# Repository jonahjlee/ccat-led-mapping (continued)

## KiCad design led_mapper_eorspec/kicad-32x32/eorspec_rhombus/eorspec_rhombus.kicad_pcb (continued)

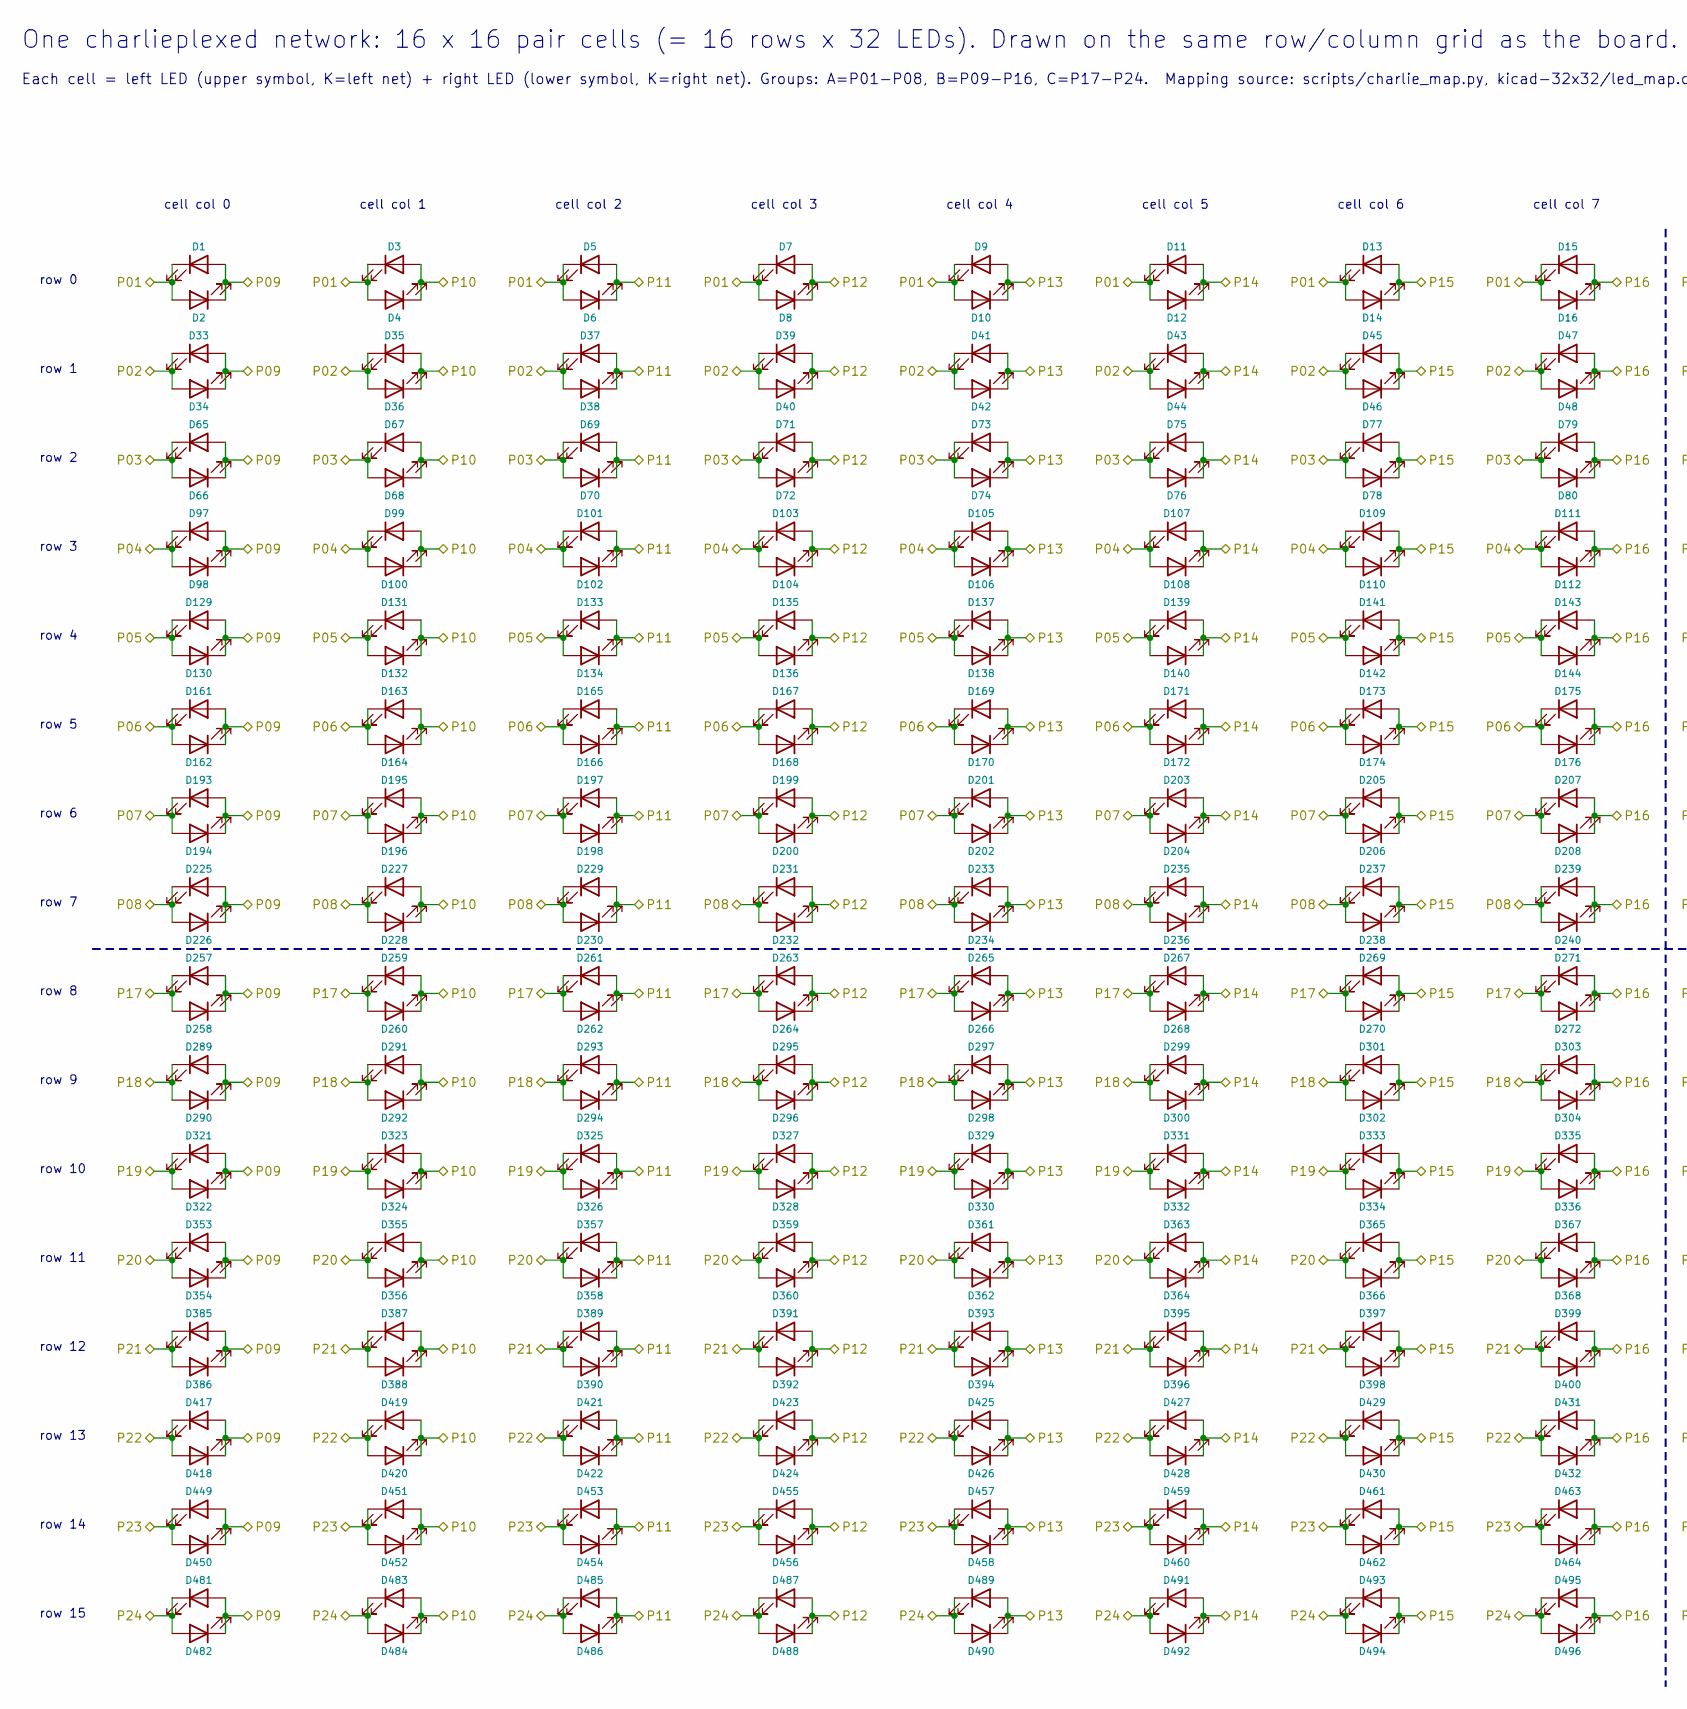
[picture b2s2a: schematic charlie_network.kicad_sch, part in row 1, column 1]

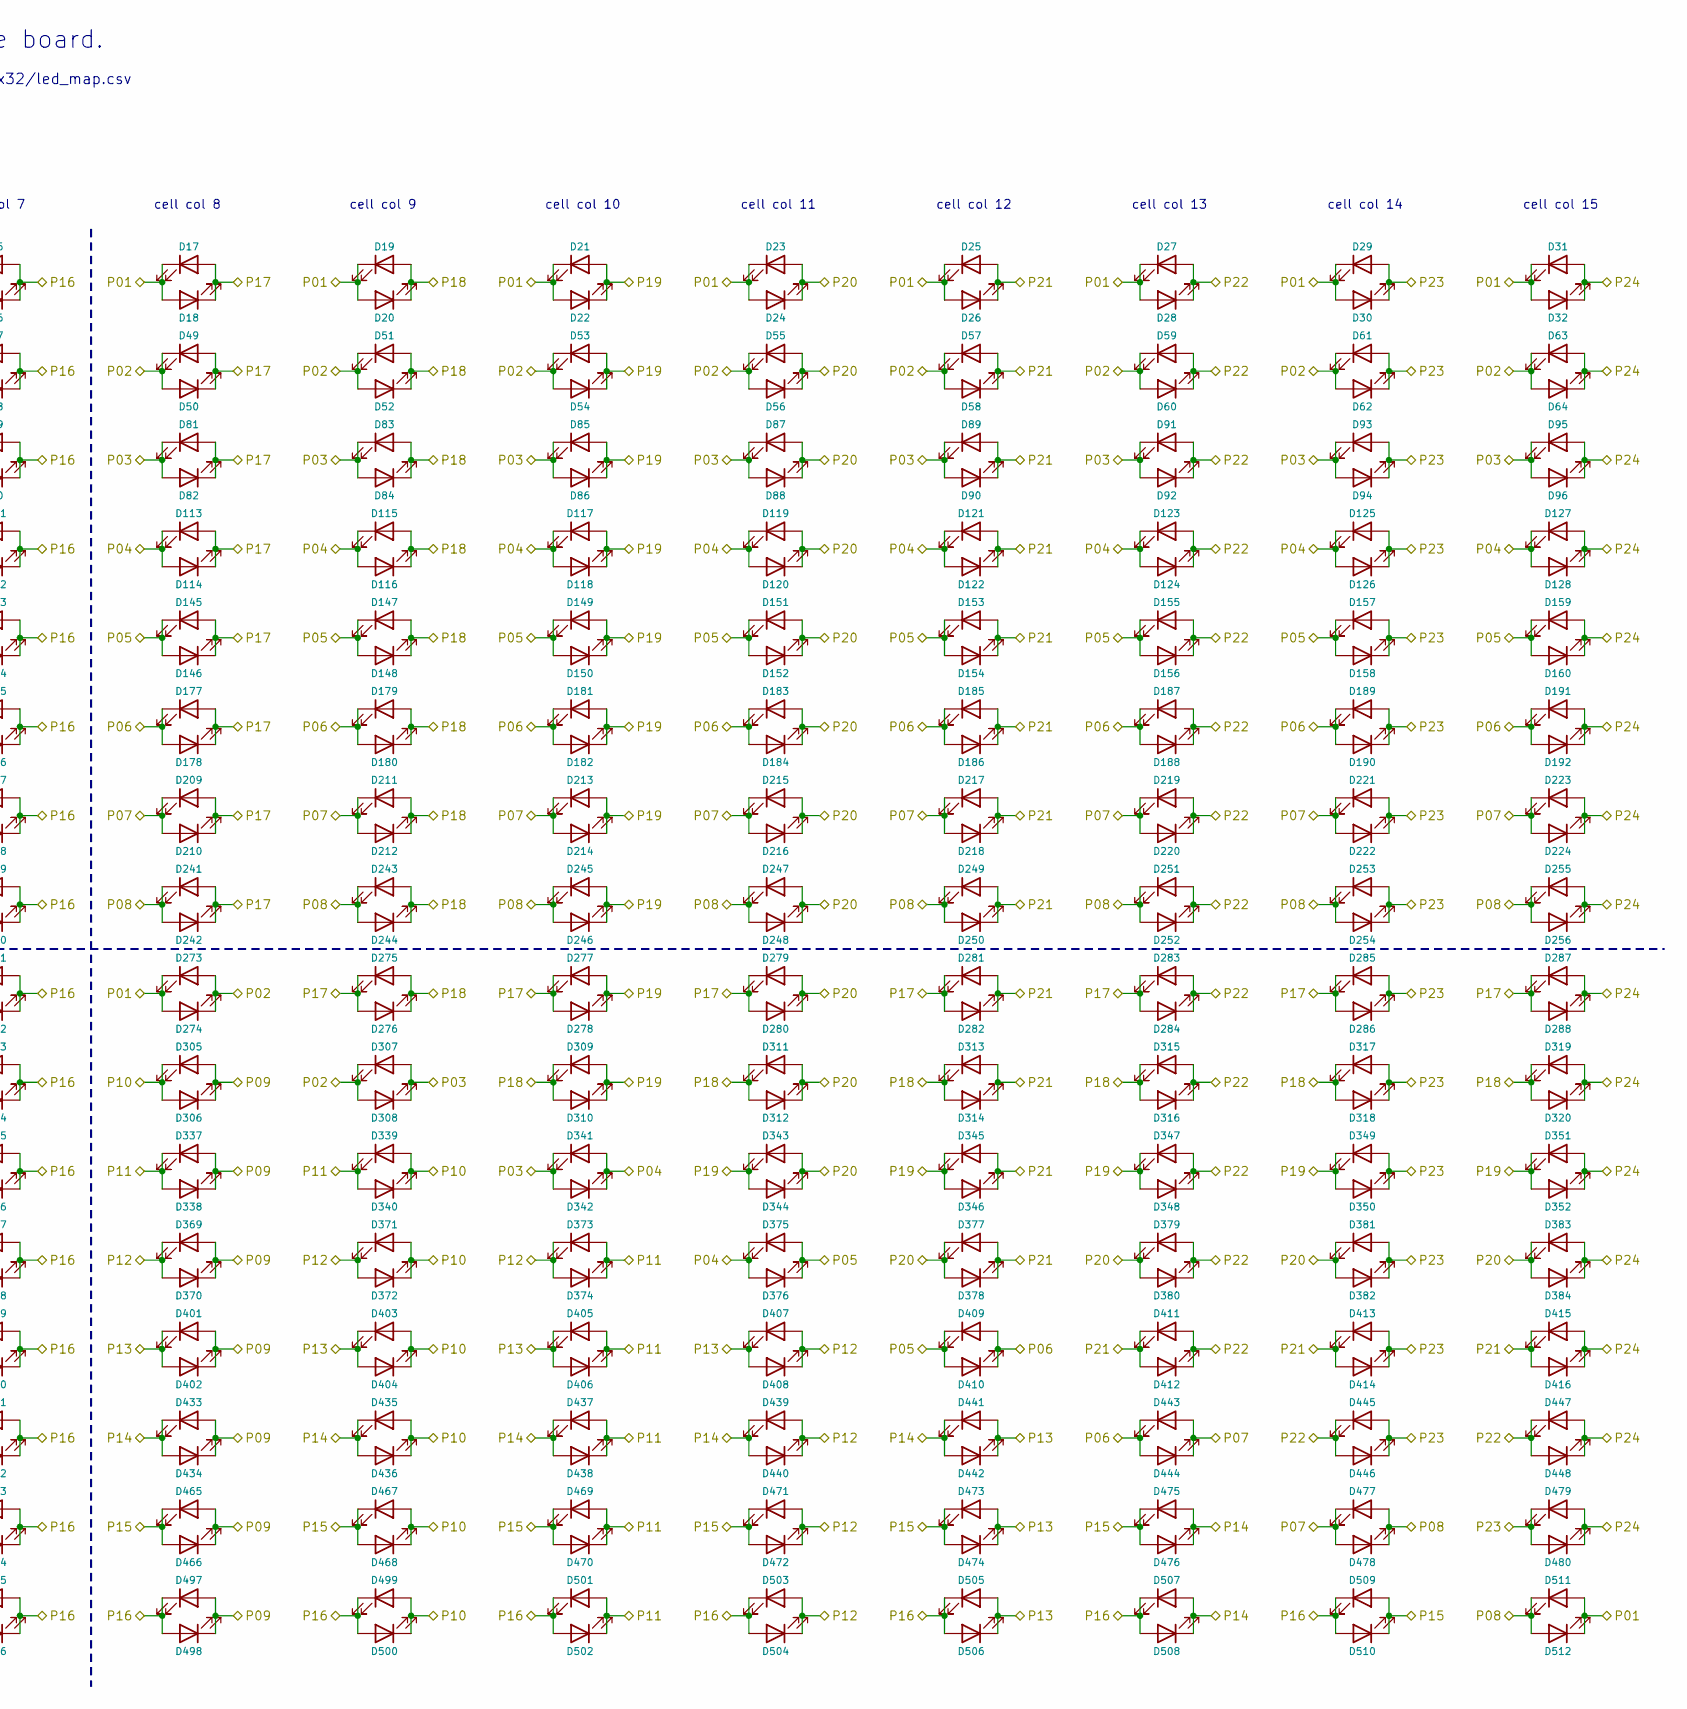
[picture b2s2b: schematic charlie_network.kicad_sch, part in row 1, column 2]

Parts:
D1, D2, D3, D4, D5, D6, D7, D8, D9, D10, D11, D12, D13, D14, D15, D16, D17, D18, D19, D20, D21, D22, D23, D24, D25, D26, D27, D28, D29, D30, D31, D32, D33, D34, D35, D36, D37, D38, D39, D40, D41, D42, D43, D44, D45, D46, D47, D48, D49, D50, D51, D52, D53, D54, D55, D56, D57, D58, D59, D60, D61, D62, D63, D64, D65, D66, D67, D68, D69, D70, D71, D72, D73, D74, D75, D76, D77, D78, D79, D80, D81, D82, D83, D84, D85, D86, D87, D88, D89, D90, D91, D92, D93, D94, D95, D96, D97, D98, D99, D100, D101, D102, D103, D104, D105, D106, D107, D108, D109, D110, D111, D112, D113, D114, D115, D116, D117, D118, D119, D120, D121, D122, D123, D124, D125, D126, D127, D128, D129, D130, D131, D132, D133, D134, D135, D136, D137, D138, D139, D140, D141, D142, D143, D144, D145, D146, D147, D148, D149, D150, D151, D152, D153, D154, D155, D156, D157, D158, D159, D160, D161, D162, D163, D164, D165, D166, D167, D168, D169, D170, D171, D172, D173, D174, D175, D176, D177, D178, D179, D180, D181, D182, D183, D184, D185, D186, D187, D188, D189, D190, D191, D192, D193, D194, D195, D196, D197, D198, D199, D200, D201, D202, D203, D204, D205, D206, D207, D208, D209, D210, D211, D212, D213, D214, D215, D216, D217, D218, D219, D220, D221, D222, D223, D224, D225, D226, D227, D228, D229, D230, D231, D232, D233, D234, D235, D236, D237, D238, D239, D240, D241, D242, D243, D244, D245, D246, D247, D248, D249, D250, D251, D252, D253, D254, D255, D256, D257, D258, D259, D260, D261, D262, D263, D264, D265, D266, D267, D268, D269, D270, D271, D272, D273, D274, D275, D276, D277, D278, D279, D280, D281, D282, D283, D284, D285, D286, D287, D288, D289, D290, D291, D292, D293, D294, D295, D296, D297, D298, D299, D300, D301, D302, D303, D304, D305, D306, D307, D308, D309, D310, D311, D312, D313, D314, D315, D316, D317, D318, D319, D320, D321, D322, D323, D324, D325, D326, D327, D328, D329, D330, D331, D332, D333, D334, D335, D336, D337, D338, D339, D340, D341, D342, D343, D344, D345, D346, D347, D348, D349, D350, D351, D352, D353, D354, D355, D356, D357, D358, D359, D360, D361, D362, D363, D364, D365, D366, D367, D368, D369, D370, D371, D372, D373, D374, D375, D376, D377, D378, D379, D380, D381, D382, D383, D384, D385, D386, D387, D388, D389, D390, D391, D392, D393, D394, D395, D396, D397, D398, D399, D400, D401, D402, D403, D404, D405, D406, D407, D408, D409, D410, D411, D412, D413, D414, D415, D416, D417, D418, D419, D420, D421, D422, D423, D424, D425, D426, D427, D428, D429, D430, D431, D432, D433, D434, D435, D436, D437, D438, D439, D440, D441, D442, D443, D444, D445, D446, D447, D448, D449, D450, D451, D452, D453, D454, D455, D456, D457, D458, D459, D460, D461, D462, D463, D464, D465, D466, D467, D468, D469, D470, D471, D472, D473, D474, D475, D476, D477, D478, D479, D480, D481, D482, D483, D484, D485, D486, D487, D488, D489, D490, D491, D492, D493, D494, D495, D496, D497, D498, D499, D500, D501, D502, D503, D504, D505, D506, D507, D508, D509, D510, D511, D512: XL-0201SURC; LED_0201_XL-0201SURC; LCSC C3646923

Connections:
P01: D1.1 (K), D2.2 (A), D3.1 (K), D4.2 (A), D5.1 (K), D6.2 (A), D7.1 (K), D8.2 (A), D9.1 (K), D10.2 (A), D11.1 (K), D12.2 (A), D13.1 (K), D14.2 (A), D15.1 (K), D16.2 (A), D17.1 (K), D18.2 (A), D19.1 (K), D20.2 (A), D21.1 (K), D22.2 (A), D23.1 (K), D24.2 (A), D25.1 (K), D26.2 (A), D27.1 (K), D28.2 (A), D29.1 (K), D30.2 (A), D31.1 (K), D32.2 (A), D273.1 (K), D274.2 (A), D511.2 (A), D512.1 (K); also elsewhere on the board
P02: D33.1 (K), D34.2 (A), D35.1 (K), D36.2 (A), D37.1 (K), D38.2 (A), D39.1 (K), D40.2 (A), D41.1 (K), D42.2 (A), D43.1 (K), D44.2 (A), D45.1 (K), D46.2 (A), D47.1 (K), D48.2 (A), D49.1 (K), D50.2 (A), D51.1 (K), D52.2 (A), D53.1 (K), D54.2 (A), D55.1 (K), D56.2 (A), D57.1 (K), D58.2 (A), D59.1 (K), D60.2 (A), D61.1 (K), D62.2 (A), D63.1 (K), D64.2 (A), D273.2 (A), D274.1 (K), D307.1 (K), D308.2 (A); also elsewhere on the board
P03: D65.1 (K), D66.2 (A), D67.1 (K), D68.2 (A), D69.1 (K), D70.2 (A), D71.1 (K), D72.2 (A), D73.1 (K), D74.2 (A), D75.1 (K), D76.2 (A), D77.1 (K), D78.2 (A), D79.1 (K), D80.2 (A), D81.1 (K), D82.2 (A), D83.1 (K), D84.2 (A), D85.1 (K), D86.2 (A), D87.1 (K), D88.2 (A), D89.1 (K), D90.2 (A), D91.1 (K), D92.2 (A), D93.1 (K), D94.2 (A), D95.1 (K), D96.2 (A), D307.2 (A), D308.1 (K), D341.1 (K), D342.2 (A); also elsewhere on the board
P04: D97.1 (K), D98.2 (A), D99.1 (K), D100.2 (A), D101.1 (K), D102.2 (A), D103.1 (K), D104.2 (A), D105.1 (K), D106.2 (A), D107.1 (K), D108.2 (A), D109.1 (K), D110.2 (A), D111.1 (K), D112.2 (A), D113.1 (K), D114.2 (A), D115.1 (K), D116.2 (A), D117.1 (K), D118.2 (A), D119.1 (K), D120.2 (A), D121.1 (K), D122.2 (A), D123.1 (K), D124.2 (A), D125.1 (K), D126.2 (A), D127.1 (K), D128.2 (A), D341.2 (A), D342.1 (K), D375.1 (K), D376.2 (A); also elsewhere on the board
P05: D129.1 (K), D130.2 (A), D131.1 (K), D132.2 (A), D133.1 (K), D134.2 (A), D135.1 (K), D136.2 (A), D137.1 (K), D138.2 (A), D139.1 (K), D140.2 (A), D141.1 (K), D142.2 (A), D143.1 (K), D144.2 (A), D145.1 (K), D146.2 (A), D147.1 (K), D148.2 (A), D149.1 (K), D150.2 (A), D151.1 (K), D152.2 (A), D153.1 (K), D154.2 (A), D155.1 (K), D156.2 (A), D157.1 (K), D158.2 (A), D159.1 (K), D160.2 (A), D375.2 (A), D376.1 (K), D409.1 (K), D410.2 (A); also elsewhere on the board
P06: D161.1 (K), D162.2 (A), D163.1 (K), D164.2 (A), D165.1 (K), D166.2 (A), D167.1 (K), D168.2 (A), D169.1 (K), D170.2 (A), D171.1 (K), D172.2 (A), D173.1 (K), D174.2 (A), D175.1 (K), D176.2 (A), D177.1 (K), D178.2 (A), D179.1 (K), D180.2 (A), D181.1 (K), D182.2 (A), D183.1 (K), D184.2 (A), D185.1 (K), D186.2 (A), D187.1 (K), D188.2 (A), D189.1 (K), D190.2 (A), D191.1 (K), D192.2 (A), D409.2 (A), D410.1 (K), D443.1 (K), D444.2 (A); also elsewhere on the board
P07: D193.1 (K), D194.2 (A), D195.1 (K), D196.2 (A), D197.1 (K), D198.2 (A), D199.1 (K), D200.2 (A), D201.1 (K), D202.2 (A), D203.1 (K), D204.2 (A), D205.1 (K), D206.2 (A), D207.1 (K), D208.2 (A), D209.1 (K), D210.2 (A), D211.1 (K), D212.2 (A), D213.1 (K), D214.2 (A), D215.1 (K), D216.2 (A), D217.1 (K), D218.2 (A), D219.1 (K), D220.2 (A), D221.1 (K), D222.2 (A), D223.1 (K), D224.2 (A), D443.2 (A), D444.1 (K), D477.1 (K), D478.2 (A); also elsewhere on the board
P08: D225.1 (K), D226.2 (A), D227.1 (K), D228.2 (A), D229.1 (K), D230.2 (A), D231.1 (K), D232.2 (A), D233.1 (K), D234.2 (A), D235.1 (K), D236.2 (A), D237.1 (K), D238.2 (A), D239.1 (K), D240.2 (A), D241.1 (K), D242.2 (A), D243.1 (K), D244.2 (A), D245.1 (K), D246.2 (A), D247.1 (K), D248.2 (A), D249.1 (K), D250.2 (A), D251.1 (K), D252.2 (A), D253.1 (K), D254.2 (A), D255.1 (K), D256.2 (A), D477.2 (A), D478.1 (K), D511.1 (K), D512.2 (A); also elsewhere on the board
P09: D1.2 (A), D2.1 (K), D33.2 (A), D34.1 (K), D65.2 (A), D66.1 (K), D97.2 (A), D98.1 (K), D129.2 (A), D130.1 (K), D161.2 (A), D162.1 (K), D193.2 (A), D194.1 (K), D225.2 (A), D226.1 (K), D257.2 (A), D258.1 (K), D289.2 (A), D290.1 (K), D305.2 (A), D306.1 (K), D321.2 (A), D322.1 (K), D337.2 (A), D338.1 (K), D353.2 (A), D354.1 (K), D369.2 (A), D370.1 (K), D385.2 (A), D386.1 (K), D401.2 (A), D402.1 (K), D417.2 (A), D418.1 (K), D433.2 (A), D434.1 (K), D449.2 (A), D450.1 (K), D465.2 (A), D466.1 (K), D481.2 (A), D482.1 (K), D497.2 (A), D498.1 (K); also elsewhere on the board
P10: D3.2 (A), D4.1 (K), D35.2 (A), D36.1 (K), D67.2 (A), D68.1 (K), D99.2 (A), D100.1 (K), D131.2 (A), D132.1 (K), D163.2 (A), D164.1 (K), D195.2 (A), D196.1 (K), D227.2 (A), D228.1 (K), D259.2 (A), D260.1 (K), D291.2 (A), D292.1 (K), D305.1 (K), D306.2 (A), D323.2 (A), D324.1 (K), D339.2 (A), D340.1 (K), D355.2 (A), D356.1 (K), D371.2 (A), D372.1 (K), D387.2 (A), D388.1 (K), D403.2 (A), D404.1 (K), D419.2 (A), D420.1 (K), D435.2 (A), D436.1 (K), D451.2 (A), D452.1 (K), D467.2 (A), D468.1 (K), D483.2 (A), D484.1 (K), D499.2 (A), D500.1 (K); also elsewhere on the board
P11: D5.2 (A), D6.1 (K), D37.2 (A), D38.1 (K), D69.2 (A), D70.1 (K), D101.2 (A), D102.1 (K), D133.2 (A), D134.1 (K), D165.2 (A), D166.1 (K), D197.2 (A), D198.1 (K), D229.2 (A), D230.1 (K), D261.2 (A), D262.1 (K), D293.2 (A), D294.1 (K), D325.2 (A), D326.1 (K), D337.1 (K), D338.2 (A), D339.1 (K), D340.2 (A), D357.2 (A), D358.1 (K), D373.2 (A), D374.1 (K), D389.2 (A), D390.1 (K), D405.2 (A), D406.1 (K), D421.2 (A), D422.1 (K), D437.2 (A), D438.1 (K), D453.2 (A), D454.1 (K), D469.2 (A), D470.1 (K), D485.2 (A), D486.1 (K), D501.2 (A), D502.1 (K); also elsewhere on the board
P12: D7.2 (A), D8.1 (K), D39.2 (A), D40.1 (K), D71.2 (A), D72.1 (K), D103.2 (A), D104.1 (K), D135.2 (A), D136.1 (K), D167.2 (A), D168.1 (K), D199.2 (A), D200.1 (K), D231.2 (A), D232.1 (K), D263.2 (A), D264.1 (K), D295.2 (A), D296.1 (K), D327.2 (A), D328.1 (K), D359.2 (A), D360.1 (K), D369.1 (K), D370.2 (A), D371.1 (K), D372.2 (A), D373.1 (K), D374.2 (A), D391.2 (A), D392.1 (K), D407.2 (A), D408.1 (K), D423.2 (A), D424.1 (K), D439.2 (A), D440.1 (K), D455.2 (A), D456.1 (K), D471.2 (A), D472.1 (K), D487.2 (A), D488.1 (K), D503.2 (A), D504.1 (K); also elsewhere on the board
P13: D9.2 (A), D10.1 (K), D41.2 (A), D42.1 (K), D73.2 (A), D74.1 (K), D105.2 (A), D106.1 (K), D137.2 (A), D138.1 (K), D169.2 (A), D170.1 (K), D201.2 (A), D202.1 (K), D233.2 (A), D234.1 (K), D265.2 (A), D266.1 (K), D297.2 (A), D298.1 (K), D329.2 (A), D330.1 (K), D361.2 (A), D362.1 (K), D393.2 (A), D394.1 (K), D401.1 (K), D402.2 (A), D403.1 (K), D404.2 (A), D405.1 (K), D406.2 (A), D407.1 (K), D408.2 (A), D425.2 (A), D426.1 (K), D441.2 (A), D442.1 (K), D457.2 (A), D458.1 (K), D473.2 (A), D474.1 (K), D489.2 (A), D490.1 (K), D505.2 (A), D506.1 (K); also elsewhere on the board
P14: D11.2 (A), D12.1 (K), D43.2 (A), D44.1 (K), D75.2 (A), D76.1 (K), D107.2 (A), D108.1 (K), D139.2 (A), D140.1 (K), D171.2 (A), D172.1 (K), D203.2 (A), D204.1 (K), D235.2 (A), D236.1 (K), D267.2 (A), D268.1 (K), D299.2 (A), D300.1 (K), D331.2 (A), D332.1 (K), D363.2 (A), D364.1 (K), D395.2 (A), D396.1 (K), D427.2 (A), D428.1 (K), D433.1 (K), D434.2 (A), D435.1 (K), D436.2 (A), D437.1 (K), D438.2 (A), D439.1 (K), D440.2 (A), D441.1 (K), D442.2 (A), D459.2 (A), D460.1 (K), D475.2 (A), D476.1 (K), D491.2 (A), D492.1 (K), D507.2 (A), D508.1 (K); also elsewhere on the board
P15: D13.2 (A), D14.1 (K), D45.2 (A), D46.1 (K), D77.2 (A), D78.1 (K), D109.2 (A), D110.1 (K), D141.2 (A), D142.1 (K), D173.2 (A), D174.1 (K), D205.2 (A), D206.1 (K), D237.2 (A), D238.1 (K), D269.2 (A), D270.1 (K), D301.2 (A), D302.1 (K), D333.2 (A), D334.1 (K), D365.2 (A), D366.1 (K), D397.2 (A), D398.1 (K), D429.2 (A), D430.1 (K), D461.2 (A), D462.1 (K), D465.1 (K), D466.2 (A), D467.1 (K), D468.2 (A), D469.1 (K), D470.2 (A), D471.1 (K), D472.2 (A), D473.1 (K), D474.2 (A), D475.1 (K), D476.2 (A), D493.2 (A), D494.1 (K), D509.2 (A), D510.1 (K); also elsewhere on the board
P16: D15.2 (A), D16.1 (K), D47.2 (A), D48.1 (K), D79.2 (A), D80.1 (K), D111.2 (A), D112.1 (K), D143.2 (A), D144.1 (K), D175.2 (A), D176.1 (K), D207.2 (A), D208.1 (K), D239.2 (A), D240.1 (K), D271.2 (A), D272.1 (K), D303.2 (A), D304.1 (K), D335.2 (A), D336.1 (K), D367.2 (A), D368.1 (K), D399.2 (A), D400.1 (K), D431.2 (A), D432.1 (K), D463.2 (A), D464.1 (K), D495.2 (A), D496.1 (K), D497.1 (K), D498.2 (A), D499.1 (K), D500.2 (A), D501.1 (K), D502.2 (A), D503.1 (K), D504.2 (A), D505.1 (K), D506.2 (A), D507.1 (K), D508.2 (A), D509.1 (K), D510.2 (A); also elsewhere on the board
P17: D17.2 (A), D18.1 (K), D49.2 (A), D50.1 (K), D81.2 (A), D82.1 (K), D113.2 (A), D114.1 (K), D145.2 (A), D146.1 (K), D177.2 (A), D178.1 (K), D209.2 (A), D210.1 (K), D241.2 (A), D242.1 (K), D257.1 (K), D258.2 (A), D259.1 (K), D260.2 (A), D261.1 (K), D262.2 (A), D263.1 (K), D264.2 (A), D265.1 (K), D266.2 (A), D267.1 (K), D268.2 (A), D269.1 (K), D270.2 (A), D271.1 (K), D272.2 (A), D275.1 (K), D276.2 (A), D277.1 (K), D278.2 (A), D279.1 (K), D280.2 (A), D281.1 (K), D282.2 (A), D283.1 (K), D284.2 (A), D285.1 (K), D286.2 (A), D287.1 (K), D288.2 (A); also elsewhere on the board
P18: D19.2 (A), D20.1 (K), D51.2 (A), D52.1 (K), D83.2 (A), D84.1 (K), D115.2 (A), D116.1 (K), D147.2 (A), D148.1 (K), D179.2 (A), D180.1 (K), D211.2 (A), D212.1 (K), D243.2 (A), D244.1 (K), D275.2 (A), D276.1 (K), D289.1 (K), D290.2 (A), D291.1 (K), D292.2 (A), D293.1 (K), D294.2 (A), D295.1 (K), D296.2 (A), D297.1 (K), D298.2 (A), D299.1 (K), D300.2 (A), D301.1 (K), D302.2 (A), D303.1 (K), D304.2 (A), D309.1 (K), D310.2 (A), D311.1 (K), D312.2 (A), D313.1 (K), D314.2 (A), D315.1 (K), D316.2 (A), D317.1 (K), D318.2 (A), D319.1 (K), D320.2 (A); also elsewhere on the board
P19: D21.2 (A), D22.1 (K), D53.2 (A), D54.1 (K), D85.2 (A), D86.1 (K), D117.2 (A), D118.1 (K), D149.2 (A), D150.1 (K), D181.2 (A), D182.1 (K), D213.2 (A), D214.1 (K), D245.2 (A), D246.1 (K), D277.2 (A), D278.1 (K), D309.2 (A), D310.1 (K), D321.1 (K), D322.2 (A), D323.1 (K), D324.2 (A), D325.1 (K), D326.2 (A), D327.1 (K), D328.2 (A), D329.1 (K), D330.2 (A), D331.1 (K), D332.2 (A), D333.1 (K), D334.2 (A), D335.1 (K), D336.2 (A), D343.1 (K), D344.2 (A), D345.1 (K), D346.2 (A), D347.1 (K), D348.2 (A), D349.1 (K), D350.2 (A), D351.1 (K), D352.2 (A); also elsewhere on the board
P20: D23.2 (A), D24.1 (K), D55.2 (A), D56.1 (K), D87.2 (A), D88.1 (K), D119.2 (A), D120.1 (K), D151.2 (A), D152.1 (K), D183.2 (A), D184.1 (K), D215.2 (A), D216.1 (K), D247.2 (A), D248.1 (K), D279.2 (A), D280.1 (K), D311.2 (A), D312.1 (K), D343.2 (A), D344.1 (K), D353.1 (K), D354.2 (A), D355.1 (K), D356.2 (A), D357.1 (K), D358.2 (A), D359.1 (K), D360.2 (A), D361.1 (K), D362.2 (A), D363.1 (K), D364.2 (A), D365.1 (K), D366.2 (A), D367.1 (K), D368.2 (A), D377.1 (K), D378.2 (A), D379.1 (K), D380.2 (A), D381.1 (K), D382.2 (A), D383.1 (K), D384.2 (A); also elsewhere on the board
P21: D25.2 (A), D26.1 (K), D57.2 (A), D58.1 (K), D89.2 (A), D90.1 (K), D121.2 (A), D122.1 (K), D153.2 (A), D154.1 (K), D185.2 (A), D186.1 (K), D217.2 (A), D218.1 (K), D249.2 (A), D250.1 (K), D281.2 (A), D282.1 (K), D313.2 (A), D314.1 (K), D345.2 (A), D346.1 (K), D377.2 (A), D378.1 (K), D385.1 (K), D386.2 (A), D387.1 (K), D388.2 (A), D389.1 (K), D390.2 (A), D391.1 (K), D392.2 (A), D393.1 (K), D394.2 (A), D395.1 (K), D396.2 (A), D397.1 (K), D398.2 (A), D399.1 (K), D400.2 (A), D411.1 (K), D412.2 (A), D413.1 (K), D414.2 (A), D415.1 (K), D416.2 (A); also elsewhere on the board
P22: D27.2 (A), D28.1 (K), D59.2 (A), D60.1 (K), D91.2 (A), D92.1 (K), D123.2 (A), D124.1 (K), D155.2 (A), D156.1 (K), D187.2 (A), D188.1 (K), D219.2 (A), D220.1 (K), D251.2 (A), D252.1 (K), D283.2 (A), D284.1 (K), D315.2 (A), D316.1 (K), D347.2 (A), D348.1 (K), D379.2 (A), D380.1 (K), D411.2 (A), D412.1 (K), D417.1 (K), D418.2 (A), D419.1 (K), D420.2 (A), D421.1 (K), D422.2 (A), D423.1 (K), D424.2 (A), D425.1 (K), D426.2 (A), D427.1 (K), D428.2 (A), D429.1 (K), D430.2 (A), D431.1 (K), D432.2 (A), D445.1 (K), D446.2 (A), D447.1 (K), D448.2 (A); also elsewhere on the board
P23: D29.2 (A), D30.1 (K), D61.2 (A), D62.1 (K), D93.2 (A), D94.1 (K), D125.2 (A), D126.1 (K), D157.2 (A), D158.1 (K), D189.2 (A), D190.1 (K), D221.2 (A), D222.1 (K), D253.2 (A), D254.1 (K), D285.2 (A), D286.1 (K), D317.2 (A), D318.1 (K), D349.2 (A), D350.1 (K), D381.2 (A), D382.1 (K), D413.2 (A), D414.1 (K), D445.2 (A), D446.1 (K), D449.1 (K), D450.2 (A), D451.1 (K), D452.2 (A), D453.1 (K), D454.2 (A), D455.1 (K), D456.2 (A), D457.1 (K), D458.2 (A), D459.1 (K), D460.2 (A), D461.1 (K), D462.2 (A), D463.1 (K), D464.2 (A), D479.1 (K), D480.2 (A); also elsewhere on the board
P24: D31.2 (A), D32.1 (K), D63.2 (A), D64.1 (K), D95.2 (A), D96.1 (K), D127.2 (A), D128.1 (K), D159.2 (A), D160.1 (K), D191.2 (A), D192.1 (K), D223.2 (A), D224.1 (K), D255.2 (A), D256.1 (K), D287.2 (A), D288.1 (K), D319.2 (A), D320.1 (K), D351.2 (A), D352.1 (K), D383.2 (A), D384.1 (K), D415.2 (A), D416.1 (K), D447.2 (A), D448.1 (K), D479.2 (A), D480.1 (K), D481.1 (K), D482.2 (A), D483.1 (K), D484.2 (A), D485.1 (K), D486.2 (A), D487.1 (K), D488.2 (A), D489.1 (K), D490.2 (A), D491.1 (K), D492.2 (A), D493.1 (K), D494.2 (A), D495.1 (K), D496.2 (A); also elsewhere on the board

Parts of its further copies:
D513, D514, D515, D516, D517, D518, D519, D520, D521, D522, D523, D524, D525, D526, D527, D528, D529, D530, D531, D532, D533, D534, D535, D536, D537, D538, D539, D540, D541, D542, D543, D544, D545, D546, D547, D548, D549, D550, D551, D552, D553, D554, D555, D556, D557, D558, D559, D560, D561, D562, D563, D564, D565, D566, D567, D568, D569, D570, D571, D572, D573, D574, D575, D576, D577, D578, D579, D580, D581, D582, D583, D584, D585, D586, D587, D588, D589, D590, D591, D592, D593, D594, D595, D596, D597, D598, D599, D600, D601, D602, D603, D604, D605, D606, D607, D608, D609, D610, D611, D612, D613, D614, D615, D616, D617, D618, D619, D620, D621, D622, D623, D624, D625, D626, D627, D628, D629, D630, D631, D632, D633, D634, D635, D636, D637, D638, D639, D640, D641, D642, D643, D644, D645, D646, D647, D648, D649, D650, D651, D652, D653, D654, D655, D656, D657, D658, D659, D660, D661, D662, D663, D664, D665, D666, D667, D668, D669, D670, D671, D672, D673, D674, D675, D676, D677, D678, D679, D680, D681, D682, D683, D684, D685, D686, D687, D688, D689, D690, D691, D692, D693, D694, D695, D696, D697, D698, D699, D700, D701, D702, D703, D704, D705, D706, D707, D708, D709, D710, D711, D712, D713, D714, D715, D716, D717, D718, D719, D720, D721, D722, D723, D724, D725, D726, D727, D728, D729, D730, D731, D732, D733, D734, D735, D736, D737, D738, D739, D740, D741, D742, D743, D744, D745, D746, D747, D748, D749, D750, D751, D752, D753, D754, D755, D756, D757, D758, D759, D760, D761, D762, D763, D764, D765, D766, D767, D768, D769, D770, D771, D772, D773, D774, D775, D776, D777, D778, D779, D780, D781, D782, D783, D784, D785, D786, D787, D788, D789, D790, D791, D792, D793, D794, D795, D796, D797, D798, D799, D800, D801, D802, D803, D804, D805, D806, D807, D808, D809, D810, D811, D812, D813, D814, D815, D816, D817, D818, D819, D820, D821, D822, D823, D824, D825, D826, D827, D828, D829, D830, D831, D832, D833, D834, D835, D836, D837, D838, D839, D840, D841, D842, D843, D844, D845, D846, D847, D848, D849, D850, D851, D852, D853, D854, D855, D856, D857, D858, D859, D860, D861, D862, D863, D864, D865, D866, D867, D868, D869, D870, D871, D872, D873, D874, D875, D876, D877, D878, D879, D880, D881, D882, D883, D884, D885, D886, D887, D888, D889, D890, D891, D892, D893, D894, D895, D896, D897, D898, D899, D900, D901, D902, D903, D904, D905, D906, D907, D908, D909, D910, D911, D912, D913, D914, D915, D916, D917, D918, D919, D920, D921, D922, D923, D924, D925, D926, D927, D928, D929, D930, D931, D932, D933, D934, D935, D936, D937, D938, D939, D940, D941, D942, D943, D944, D945, D946, D947, D948, D949, D950, D951, D952, D953, D954, D955, D956, D957, D958, D959, D960, D961, D962, D963, D964, D965, D966, D967, D968, D969, D970, D971, D972, D973, D974, D975, D976, D977, D978, D979, D980, D981, D982, D983, D984, D985, D986, D987, D988, D989, D990, D991, D992, D993, D994, D995, D996, D997, D998, D999, D1000, D1001, D1002, D1003, D1004, D1005, D1006, D1007, D1008, D1009, D1010, D1011, D1012, D1013, D1014, D1015, D1016, D1017, D1018, D1019, D1020, D1021, D1022, D1023, D1024: XL-0201SURC; LED_0201_XL-0201SURC; LCSC C3646923

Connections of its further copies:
P01: D513.1 (K), D514.2 (A), D515.1 (K), D516.2 (A), D517.1 (K), D518.2 (A), D519.1 (K), D520.2 (A), D521.1 (K), D522.2 (A), D523.1 (K), D524.2 (A), D525.1 (K), D526.2 (A), D527.1 (K), D528.2 (A), D529.1 (K), D530.2 (A), D531.1 (K), D532.2 (A), D533.1 (K), D534.2 (A), D535.1 (K), D536.2 (A), D537.1 (K), D538.2 (A), D539.1 (K), D540.2 (A), D541.1 (K), D542.2 (A), D543.1 (K), D544.2 (A), D785.1 (K), D786.2 (A), D1023.2 (A), D1024.1 (K); also elsewhere on the board
P02: D545.1 (K), D546.2 (A), D547.1 (K), D548.2 (A), D549.1 (K), D550.2 (A), D551.1 (K), D552.2 (A), D553.1 (K), D554.2 (A), D555.1 (K), D556.2 (A), D557.1 (K), D558.2 (A), D559.1 (K), D560.2 (A), D561.1 (K), D562.2 (A), D563.1 (K), D564.2 (A), D565.1 (K), D566.2 (A), D567.1 (K), D568.2 (A), D569.1 (K), D570.2 (A), D571.1 (K), D572.2 (A), D573.1 (K), D574.2 (A), D575.1 (K), D576.2 (A), D785.2 (A), D786.1 (K), D819.1 (K), D820.2 (A); also elsewhere on the board
P03: D577.1 (K), D578.2 (A), D579.1 (K), D580.2 (A), D581.1 (K), D582.2 (A), D583.1 (K), D584.2 (A), D585.1 (K), D586.2 (A), D587.1 (K), D588.2 (A), D589.1 (K), D590.2 (A), D591.1 (K), D592.2 (A), D593.1 (K), D594.2 (A), D595.1 (K), D596.2 (A), D597.1 (K), D598.2 (A), D599.1 (K), D600.2 (A), D601.1 (K), D602.2 (A), D603.1 (K), D604.2 (A), D605.1 (K), D606.2 (A), D607.1 (K), D608.2 (A), D819.2 (A), D820.1 (K), D853.1 (K), D854.2 (A); also elsewhere on the board
P04: D609.1 (K), D610.2 (A), D611.1 (K), D612.2 (A), D613.1 (K), D614.2 (A), D615.1 (K), D616.2 (A), D617.1 (K), D618.2 (A), D619.1 (K), D620.2 (A), D621.1 (K), D622.2 (A), D623.1 (K), D624.2 (A), D625.1 (K), D626.2 (A), D627.1 (K), D628.2 (A), D629.1 (K), D630.2 (A), D631.1 (K), D632.2 (A), D633.1 (K), D634.2 (A), D635.1 (K), D636.2 (A), D637.1 (K), D638.2 (A), D639.1 (K), D640.2 (A), D853.2 (A), D854.1 (K), D887.1 (K), D888.2 (A); also elsewhere on the board
P05: D641.1 (K), D642.2 (A), D643.1 (K), D644.2 (A), D645.1 (K), D646.2 (A), D647.1 (K), D648.2 (A), D649.1 (K), D650.2 (A), D651.1 (K), D652.2 (A), D653.1 (K), D654.2 (A), D655.1 (K), D656.2 (A), D657.1 (K), D658.2 (A), D659.1 (K), D660.2 (A), D661.1 (K), D662.2 (A), D663.1 (K), D664.2 (A), D665.1 (K), D666.2 (A), D667.1 (K), D668.2 (A), D669.1 (K), D670.2 (A), D671.1 (K), D672.2 (A), D887.2 (A), D888.1 (K), D921.1 (K), D922.2 (A); also elsewhere on the board
P06: D673.1 (K), D674.2 (A), D675.1 (K), D676.2 (A), D677.1 (K), D678.2 (A), D679.1 (K), D680.2 (A), D681.1 (K), D682.2 (A), D683.1 (K), D684.2 (A), D685.1 (K), D686.2 (A), D687.1 (K), D688.2 (A), D689.1 (K), D690.2 (A), D691.1 (K), D692.2 (A), D693.1 (K), D694.2 (A), D695.1 (K), D696.2 (A), D697.1 (K), D698.2 (A), D699.1 (K), D700.2 (A), D701.1 (K), D702.2 (A), D703.1 (K), D704.2 (A), D921.2 (A), D922.1 (K), D955.1 (K), D956.2 (A); also elsewhere on the board
P07: D705.1 (K), D706.2 (A), D707.1 (K), D708.2 (A), D709.1 (K), D710.2 (A), D711.1 (K), D712.2 (A), D713.1 (K), D714.2 (A), D715.1 (K), D716.2 (A), D717.1 (K), D718.2 (A), D719.1 (K), D720.2 (A), D721.1 (K), D722.2 (A), D723.1 (K), D724.2 (A), D725.1 (K), D726.2 (A), D727.1 (K), D728.2 (A), D729.1 (K), D730.2 (A), D731.1 (K), D732.2 (A), D733.1 (K), D734.2 (A), D735.1 (K), D736.2 (A), D955.2 (A), D956.1 (K), D989.1 (K), D990.2 (A); also elsewhere on the board
P08: D737.1 (K), D738.2 (A), D739.1 (K), D740.2 (A), D741.1 (K), D742.2 (A), D743.1 (K), D744.2 (A), D745.1 (K), D746.2 (A), D747.1 (K), D748.2 (A), D749.1 (K), D750.2 (A), D751.1 (K), D752.2 (A), D753.1 (K), D754.2 (A), D755.1 (K), D756.2 (A), D757.1 (K), D758.2 (A), D759.1 (K), D760.2 (A), D761.1 (K), D762.2 (A), D763.1 (K), D764.2 (A), D765.1 (K), D766.2 (A), D767.1 (K), D768.2 (A), D989.2 (A), D990.1 (K), D1023.1 (K), D1024.2 (A); also elsewhere on the board
P09: D513.2 (A), D514.1 (K), D545.2 (A), D546.1 (K), D577.2 (A), D578.1 (K), D609.2 (A), D610.1 (K), D641.2 (A), D642.1 (K), D673.2 (A), D674.1 (K), D705.2 (A), D706.1 (K), D737.2 (A), D738.1 (K), D769.2 (A), D770.1 (K), D801.2 (A), D802.1 (K), D817.2 (A), D818.1 (K), D833.2 (A), D834.1 (K), D849.2 (A), D850.1 (K), D865.2 (A), D866.1 (K), D881.2 (A), D882.1 (K), D897.2 (A), D898.1 (K), D913.2 (A), D914.1 (K), D929.2 (A), D930.1 (K), D945.2 (A), D946.1 (K), D961.2 (A), D962.1 (K), D977.2 (A), D978.1 (K), D993.2 (A), D994.1 (K), D1009.2 (A), D1010.1 (K); also elsewhere on the board
P10: D515.2 (A), D516.1 (K), D547.2 (A), D548.1 (K), D579.2 (A), D580.1 (K), D611.2 (A), D612.1 (K), D643.2 (A), D644.1 (K), D675.2 (A), D676.1 (K), D707.2 (A), D708.1 (K), D739.2 (A), D740.1 (K), D771.2 (A), D772.1 (K), D803.2 (A), D804.1 (K), D817.1 (K), D818.2 (A), D835.2 (A), D836.1 (K), D851.2 (A), D852.1 (K), D867.2 (A), D868.1 (K), D883.2 (A), D884.1 (K), D899.2 (A), D900.1 (K), D915.2 (A), D916.1 (K), D931.2 (A), D932.1 (K), D947.2 (A), D948.1 (K), D963.2 (A), D964.1 (K), D979.2 (A), D980.1 (K), D995.2 (A), D996.1 (K), D1011.2 (A), D1012.1 (K); also elsewhere on the board
P11: D517.2 (A), D518.1 (K), D549.2 (A), D550.1 (K), D581.2 (A), D582.1 (K), D613.2 (A), D614.1 (K), D645.2 (A), D646.1 (K), D677.2 (A), D678.1 (K), D709.2 (A), D710.1 (K), D741.2 (A), D742.1 (K), D773.2 (A), D774.1 (K), D805.2 (A), D806.1 (K), D837.2 (A), D838.1 (K), D849.1 (K), D850.2 (A), D851.1 (K), D852.2 (A), D869.2 (A), D870.1 (K), D885.2 (A), D886.1 (K), D901.2 (A), D902.1 (K), D917.2 (A), D918.1 (K), D933.2 (A), D934.1 (K), D949.2 (A), D950.1 (K), D965.2 (A), D966.1 (K), D981.2 (A), D982.1 (K), D997.2 (A), D998.1 (K), D1013.2 (A), D1014.1 (K); also elsewhere on the board
P12: D519.2 (A), D520.1 (K), D551.2 (A), D552.1 (K), D583.2 (A), D584.1 (K), D615.2 (A), D616.1 (K), D647.2 (A), D648.1 (K), D679.2 (A), D680.1 (K), D711.2 (A), D712.1 (K), D743.2 (A), D744.1 (K), D775.2 (A), D776.1 (K), D807.2 (A), D808.1 (K), D839.2 (A), D840.1 (K), D871.2 (A), D872.1 (K), D881.1 (K), D882.2 (A), D883.1 (K), D884.2 (A), D885.1 (K), D886.2 (A), D903.2 (A), D904.1 (K), D919.2 (A), D920.1 (K), D935.2 (A), D936.1 (K), D951.2 (A), D952.1 (K), D967.2 (A), D968.1 (K), D983.2 (A), D984.1 (K), D999.2 (A), D1000.1 (K), D1015.2 (A), D1016.1 (K); also elsewhere on the board
P13: D521.2 (A), D522.1 (K), D553.2 (A), D554.1 (K), D585.2 (A), D586.1 (K), D617.2 (A), D618.1 (K), D649.2 (A), D650.1 (K), D681.2 (A), D682.1 (K), D713.2 (A), D714.1 (K), D745.2 (A), D746.1 (K), D777.2 (A), D778.1 (K), D809.2 (A), D810.1 (K), D841.2 (A), D842.1 (K), D873.2 (A), D874.1 (K), D905.2 (A), D906.1 (K), D913.1 (K), D914.2 (A), D915.1 (K), D916.2 (A), D917.1 (K), D918.2 (A), D919.1 (K), D920.2 (A), D937.2 (A), D938.1 (K), D953.2 (A), D954.1 (K), D969.2 (A), D970.1 (K), D985.2 (A), D986.1 (K), D1001.2 (A), D1002.1 (K), D1017.2 (A), D1018.1 (K); also elsewhere on the board
P14: D523.2 (A), D524.1 (K), D555.2 (A), D556.1 (K), D587.2 (A), D588.1 (K), D619.2 (A), D620.1 (K), D651.2 (A), D652.1 (K), D683.2 (A), D684.1 (K), D715.2 (A), D716.1 (K), D747.2 (A), D748.1 (K), D779.2 (A), D780.1 (K), D811.2 (A), D812.1 (K), D843.2 (A), D844.1 (K), D875.2 (A), D876.1 (K), D907.2 (A), D908.1 (K), D939.2 (A), D940.1 (K), D945.1 (K), D946.2 (A), D947.1 (K), D948.2 (A), D949.1 (K), D950.2 (A), D951.1 (K), D952.2 (A), D953.1 (K), D954.2 (A), D971.2 (A), D972.1 (K), D987.2 (A), D988.1 (K), D1003.2 (A), D1004.1 (K), D1019.2 (A), D1020.1 (K); also elsewhere on the board
P15: D525.2 (A), D526.1 (K), D557.2 (A), D558.1 (K), D589.2 (A), D590.1 (K), D621.2 (A), D622.1 (K), D653.2 (A), D654.1 (K), D685.2 (A), D686.1 (K), D717.2 (A), D718.1 (K), D749.2 (A), D750.1 (K), D781.2 (A), D782.1 (K), D813.2 (A), D814.1 (K), D845.2 (A), D846.1 (K), D877.2 (A), D878.1 (K), D909.2 (A), D910.1 (K), D941.2 (A), D942.1 (K), D973.2 (A), D974.1 (K), D977.1 (K), D978.2 (A), D979.1 (K), D980.2 (A), D981.1 (K), D982.2 (A), D983.1 (K), D984.2 (A), D985.1 (K), D986.2 (A), D987.1 (K), D988.2 (A), D1005.2 (A), D1006.1 (K), D1021.2 (A), D1022.1 (K); also elsewhere on the board
P16: D527.2 (A), D528.1 (K), D559.2 (A), D560.1 (K), D591.2 (A), D592.1 (K), D623.2 (A), D624.1 (K), D655.2 (A), D656.1 (K), D687.2 (A), D688.1 (K), D719.2 (A), D720.1 (K), D751.2 (A), D752.1 (K), D783.2 (A), D784.1 (K), D815.2 (A), D816.1 (K), D847.2 (A), D848.1 (K), D879.2 (A), D880.1 (K), D911.2 (A), D912.1 (K), D943.2 (A), D944.1 (K), D975.2 (A), D976.1 (K), D1007.2 (A), D1008.1 (K), D1009.1 (K), D1010.2 (A), D1011.1 (K), D1012.2 (A), D1013.1 (K), D1014.2 (A), D1015.1 (K), D1016.2 (A), D1017.1 (K), D1018.2 (A), D1019.1 (K), D1020.2 (A), D1021.1 (K), D1022.2 (A); also elsewhere on the board
P17: D529.2 (A), D530.1 (K), D561.2 (A), D562.1 (K), D593.2 (A), D594.1 (K), D625.2 (A), D626.1 (K), D657.2 (A), D658.1 (K), D689.2 (A), D690.1 (K), D721.2 (A), D722.1 (K), D753.2 (A), D754.1 (K), D769.1 (K), D770.2 (A), D771.1 (K), D772.2 (A), D773.1 (K), D774.2 (A), D775.1 (K), D776.2 (A), D777.1 (K), D778.2 (A), D779.1 (K), D780.2 (A), D781.1 (K), D782.2 (A), D783.1 (K), D784.2 (A), D787.1 (K), D788.2 (A), D789.1 (K), D790.2 (A), D791.1 (K), D792.2 (A), D793.1 (K), D794.2 (A), D795.1 (K), D796.2 (A), D797.1 (K), D798.2 (A), D799.1 (K), D800.2 (A); also elsewhere on the board
P18: D531.2 (A), D532.1 (K), D563.2 (A), D564.1 (K), D595.2 (A), D596.1 (K), D627.2 (A), D628.1 (K), D659.2 (A), D660.1 (K), D691.2 (A), D692.1 (K), D723.2 (A), D724.1 (K), D755.2 (A), D756.1 (K), D787.2 (A), D788.1 (K), D801.1 (K), D802.2 (A), D803.1 (K), D804.2 (A), D805.1 (K), D806.2 (A), D807.1 (K), D808.2 (A), D809.1 (K), D810.2 (A), D811.1 (K), D812.2 (A), D813.1 (K), D814.2 (A), D815.1 (K), D816.2 (A), D821.1 (K), D822.2 (A), D823.1 (K), D824.2 (A), D825.1 (K), D826.2 (A), D827.1 (K), D828.2 (A), D829.1 (K), D830.2 (A), D831.1 (K), D832.2 (A); also elsewhere on the board
P19: D533.2 (A), D534.1 (K), D565.2 (A), D566.1 (K), D597.2 (A), D598.1 (K), D629.2 (A), D630.1 (K), D661.2 (A), D662.1 (K), D693.2 (A), D694.1 (K), D725.2 (A), D726.1 (K), D757.2 (A), D758.1 (K), D789.2 (A), D790.1 (K), D821.2 (A), D822.1 (K), D833.1 (K), D834.2 (A), D835.1 (K), D836.2 (A), D837.1 (K), D838.2 (A), D839.1 (K), D840.2 (A), D841.1 (K), D842.2 (A), D843.1 (K), D844.2 (A), D845.1 (K), D846.2 (A), D847.1 (K), D848.2 (A), D855.1 (K), D856.2 (A), D857.1 (K), D858.2 (A), D859.1 (K), D860.2 (A), D861.1 (K), D862.2 (A), D863.1 (K), D864.2 (A); also elsewhere on the board
P20: D535.2 (A), D536.1 (K), D567.2 (A), D568.1 (K), D599.2 (A), D600.1 (K), D631.2 (A), D632.1 (K), D663.2 (A), D664.1 (K), D695.2 (A), D696.1 (K), D727.2 (A), D728.1 (K), D759.2 (A), D760.1 (K), D791.2 (A), D792.1 (K), D823.2 (A), D824.1 (K), D855.2 (A), D856.1 (K), D865.1 (K), D866.2 (A), D867.1 (K), D868.2 (A), D869.1 (K), D870.2 (A), D871.1 (K), D872.2 (A), D873.1 (K), D874.2 (A), D875.1 (K), D876.2 (A), D877.1 (K), D878.2 (A), D879.1 (K), D880.2 (A), D889.1 (K), D890.2 (A), D891.1 (K), D892.2 (A), D893.1 (K), D894.2 (A), D895.1 (K), D896.2 (A); also elsewhere on the board
P21: D537.2 (A), D538.1 (K), D569.2 (A), D570.1 (K), D601.2 (A), D602.1 (K), D633.2 (A), D634.1 (K), D665.2 (A), D666.1 (K), D697.2 (A), D698.1 (K), D729.2 (A), D730.1 (K), D761.2 (A), D762.1 (K), D793.2 (A), D794.1 (K), D825.2 (A), D826.1 (K), D857.2 (A), D858.1 (K), D889.2 (A), D890.1 (K), D897.1 (K), D898.2 (A), D899.1 (K), D900.2 (A), D901.1 (K), D902.2 (A), D903.1 (K), D904.2 (A), D905.1 (K), D906.2 (A), D907.1 (K), D908.2 (A), D909.1 (K), D910.2 (A), D911.1 (K), D912.2 (A), D923.1 (K), D924.2 (A), D925.1 (K), D926.2 (A), D927.1 (K), D928.2 (A); also elsewhere on the board
P22: D539.2 (A), D540.1 (K), D571.2 (A), D572.1 (K), D603.2 (A), D604.1 (K), D635.2 (A), D636.1 (K), D667.2 (A), D668.1 (K), D699.2 (A), D700.1 (K), D731.2 (A), D732.1 (K), D763.2 (A), D764.1 (K), D795.2 (A), D796.1 (K), D827.2 (A), D828.1 (K), D859.2 (A), D860.1 (K), D891.2 (A), D892.1 (K), D923.2 (A), D924.1 (K), D929.1 (K), D930.2 (A), D931.1 (K), D932.2 (A), D933.1 (K), D934.2 (A), D935.1 (K), D936.2 (A), D937.1 (K), D938.2 (A), D939.1 (K), D940.2 (A), D941.1 (K), D942.2 (A), D943.1 (K), D944.2 (A), D957.1 (K), D958.2 (A), D959.1 (K), D960.2 (A); also elsewhere on the board
P23: D541.2 (A), D542.1 (K), D573.2 (A), D574.1 (K), D605.2 (A), D606.1 (K), D637.2 (A), D638.1 (K), D669.2 (A), D670.1 (K), D701.2 (A), D702.1 (K), D733.2 (A), D734.1 (K), D765.2 (A), D766.1 (K), D797.2 (A), D798.1 (K), D829.2 (A), D830.1 (K), D861.2 (A), D862.1 (K), D893.2 (A), D894.1 (K), D925.2 (A), D926.1 (K), D957.2 (A), D958.1 (K), D961.1 (K), D962.2 (A), D963.1 (K), D964.2 (A), D965.1 (K), D966.2 (A), D967.1 (K), D968.2 (A), D969.1 (K), D970.2 (A), D971.1 (K), D972.2 (A), D973.1 (K), D974.2 (A), D975.1 (K), D976.2 (A), D991.1 (K), D992.2 (A); also elsewhere on the board
P24: D543.2 (A), D544.1 (K), D575.2 (A), D576.1 (K), D607.2 (A), D608.1 (K), D639.2 (A), D640.1 (K), D671.2 (A), D672.1 (K), D703.2 (A), D704.1 (K), D735.2 (A), D736.1 (K), D767.2 (A), D768.1 (K), D799.2 (A), D800.1 (K), D831.2 (A), D832.1 (K), D863.2 (A), D864.1 (K), D895.2 (A), D896.1 (K), D927.2 (A), D928.1 (K), D959.2 (A), D960.1 (K), D991.2 (A), D992.1 (K), D993.1 (K), D994.2 (A), D995.1 (K), D996.2 (A), D997.1 (K), D998.2 (A), D999.1 (K), D1000.2 (A), D1001.1 (K), D1002.2 (A), D1003.1 (K), D1004.2 (A), D1005.1 (K), D1006.2 (A), D1007.1 (K), D1008.2 (A); also elsewhere on the board

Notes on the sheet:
One charlieplexed network: 16 x 16 pair cells (= 16 rows x 32 LEDs). Drawn on the same row/column grid as the board.
Each cell = left LED (upper symbol, K=left net) + right LED (lower symbol, K=right net). Groups: A=P01-P08, B=P09-P16, C=P17-P24. Mapping source: scripts/charlie_map.py, kicad-32x32/led_map.csv
cell col 0
cell col 1
cell col 2
cell col 3
cell col 4
cell col 5
cell col 6
cell col 7
cell col 8
cell col 9
cell col 10
cell col 11
cell col 12
cell col 13
cell col 14
cell col 15
row 0
row 1
row 2
row 3
row 4
row 5
row 6
row 7
row 8
row 9
row 10
row 11
row 12
row 13
row 14
row 15

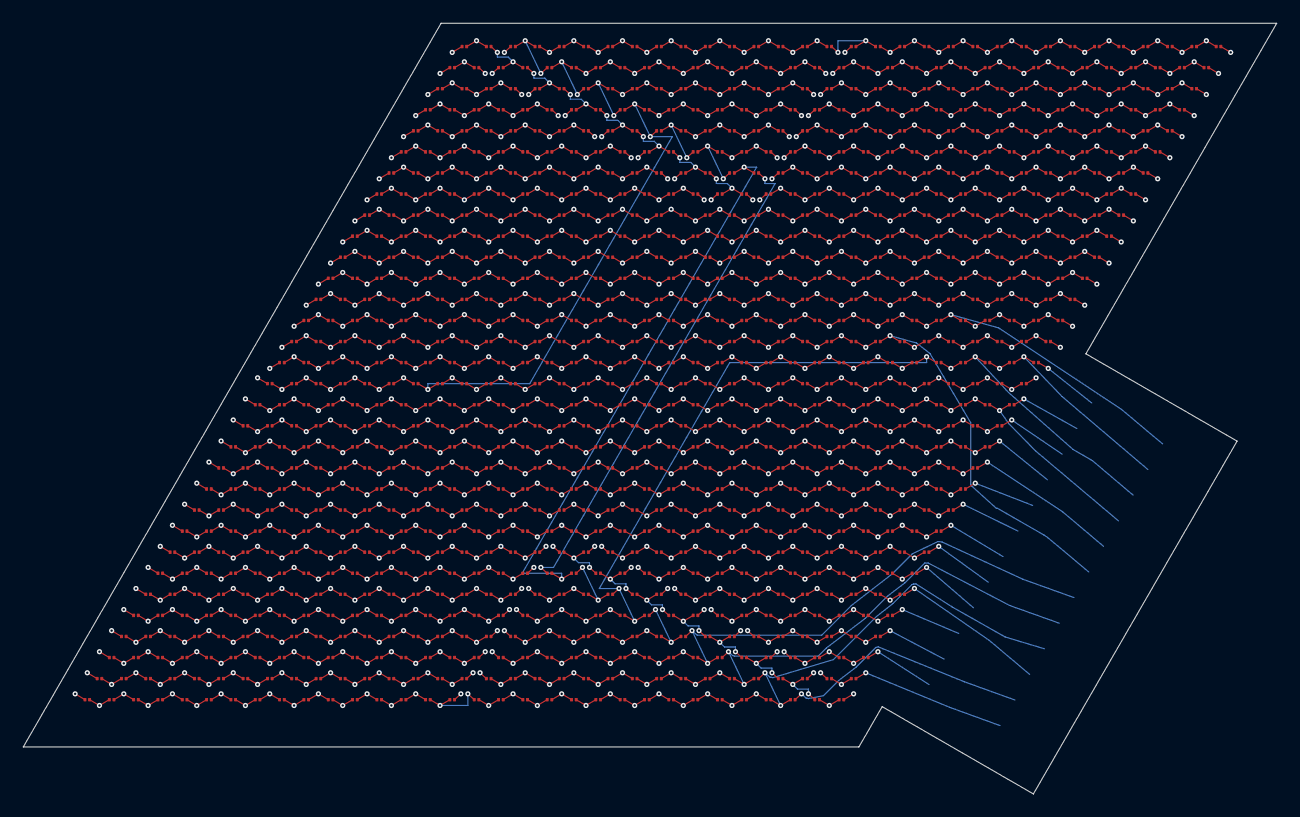
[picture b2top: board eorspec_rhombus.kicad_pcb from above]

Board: 4 copper layers, 107.7 x 66.2 mm, 1025 parts (1 on the bottom side), 24 nets.
